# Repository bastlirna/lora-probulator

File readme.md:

# LoRa Probulator

*Yat Another LoRaWAN Tester*

<br>

## Motivation

TBD

## Key Features

- Send LoRaWAN message on button press
- Periodic sending
- Configurable message parameters (confirmation, payload, SF, etc.)
- Multiple device (ABP/OTAA, several keys configuration for testing several network providers)  

For more detail about features see [Firmware project](https://github.com/bastlirna/lora-probulator/projects/1) where are list of all ideas, selected requirements and progress of its implementation.

## Build

### Hardware

What do you need:

- [BOM](hw/bom.md)
- [PCB](https://github.com/bastlirna/lora-probulator/blob/master/hw/pcb/lora-tester-top.png)
- [3D printed enclosure ](https://github.com/bastlirna/lora-probulator/blob/master/hw/enclosure/stl/_full_preview.stl) 

For more detail see [schematics](https://github.com/bastlirna/lora-probulator/blob/master/hw/lora-tester.pdf).

### Firmware

FW is written in [Arduino libraries for ESP32](https://github.com/espressif/arduino-esp32) and build with [PlatformIO](http://platformio.org/).

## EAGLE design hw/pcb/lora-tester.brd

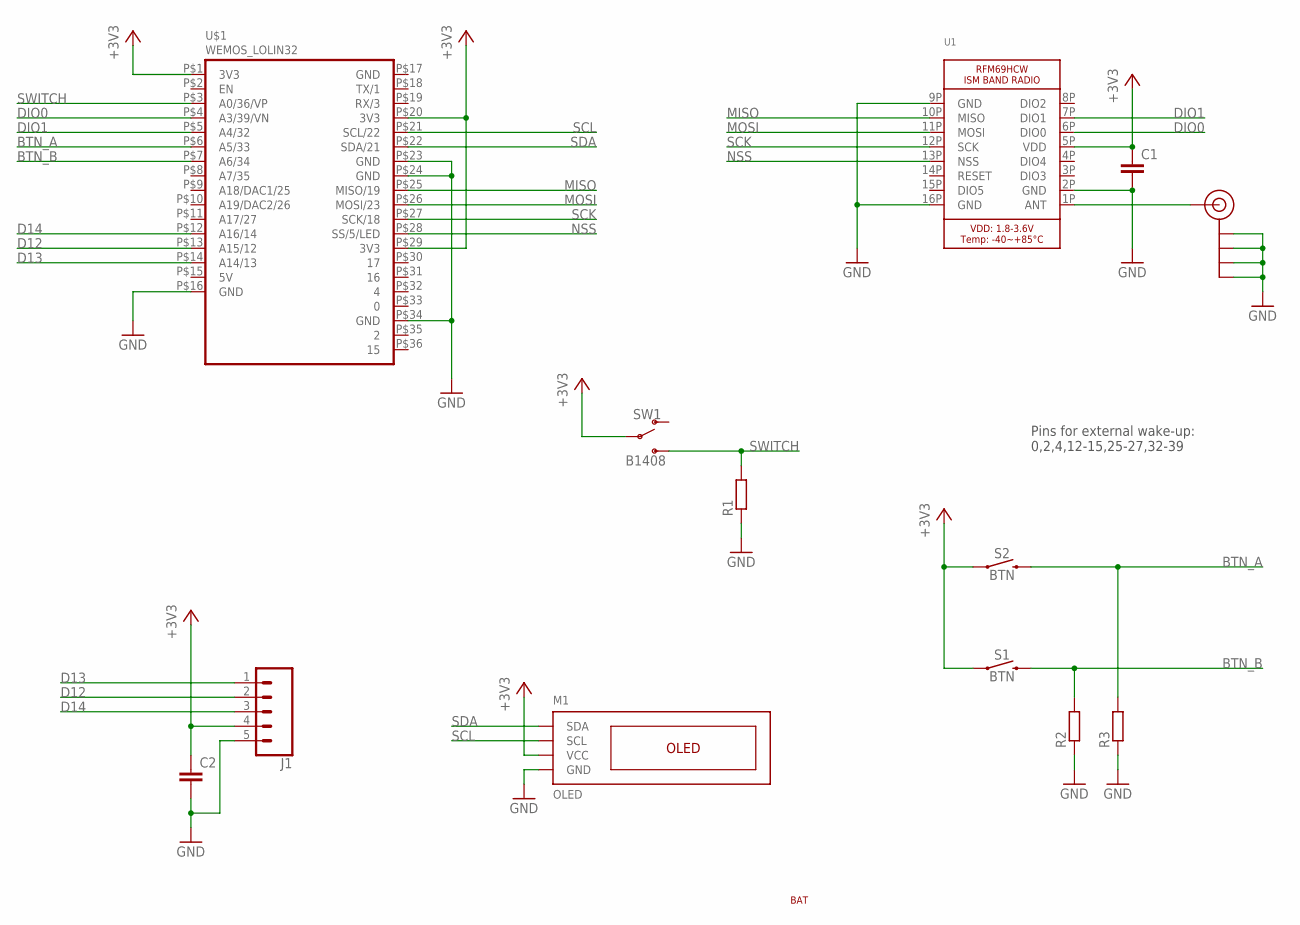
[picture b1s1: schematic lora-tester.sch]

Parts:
BAT: BAT
C1, C2: C-EUC1206; C1206
J1: CONN_05PTH_LONGPADS; 1X05_LONGPADS
J$2: SMA_EDGE; SMA-EDGE
M1: OLED
R1, R2, R3: R-EU_R0805; R0805
S1, S2: BTN; TACTILE_SWITCH_SMD_6.2MM_TALL
SW1: B1408; P-B1408
U1: RFM69HCW_SMT; RFMHCW_SMT
U$1: WEMOS_LOLIN32

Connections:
+3V3: C1.1, C2.1, J1.4, M1.VCC, S1.A2 (1), S2.A2 (1), SW1.P, U1.5P (VDD), U$1.P$1 (3V3), U$1.P$20 (3V3), U$1.P$29 (3V3)
BTN_A: R3.2, S2.B2 (2), U$1.P$6 (A5/33)
BTN_B: R2.2, S1.B2 (2), U$1.P$7 (A6/34)
D12: J1.2, U$1.P$13 (A15/12)
D13: J1.1, U$1.P$14 (A14/13)
D14: J1.3, U$1.P$12 (A16/14)
DIO0: U1.6P (DIO0), U$1.P$4 (A3/39/VN)
DIO1: U1.7P (DIO1), U$1.P$5 (A4/32)
GND: C1.2, C2.2, J1.5, J$2.GND@0 (GND), J$2.GND@1 (GND), J$2.GND@2 (GND), J$2.GND@3 (GND), M1.GND, R1.1, R2.1, R3.1, U1.2P (GND), U1.9P (GND), U1.16P (GND), U$1.P$16 (GND), U$1.P$23 (GND), U$1.P$24 (GND), U$1.P$34 (GND)
MISO: U1.10P (MISO), U$1.P$25 (MISO/19)
MOSI: U1.11P (MOSI), U$1.P$26 (MOSI/23)
unnamed: J$2.SIG (SIGNAL), U1.1P (ANT)
NSS: U1.13P (NSS), U$1.P$28 (SS/5/LED)
SCK: U1.12P (SCK), U$1.P$27 (SCK/18)
SCL: M1.SCL, U$1.P$21 (SCL/22)
SDA: M1.SDA, U$1.P$22 (SDA/21)
SWITCH: R1.2, SW1.S, U$1.P$3 (A0/36/VP)

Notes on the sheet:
Pins for external wake-up: 0,2,4,12-15,25-27,32-39

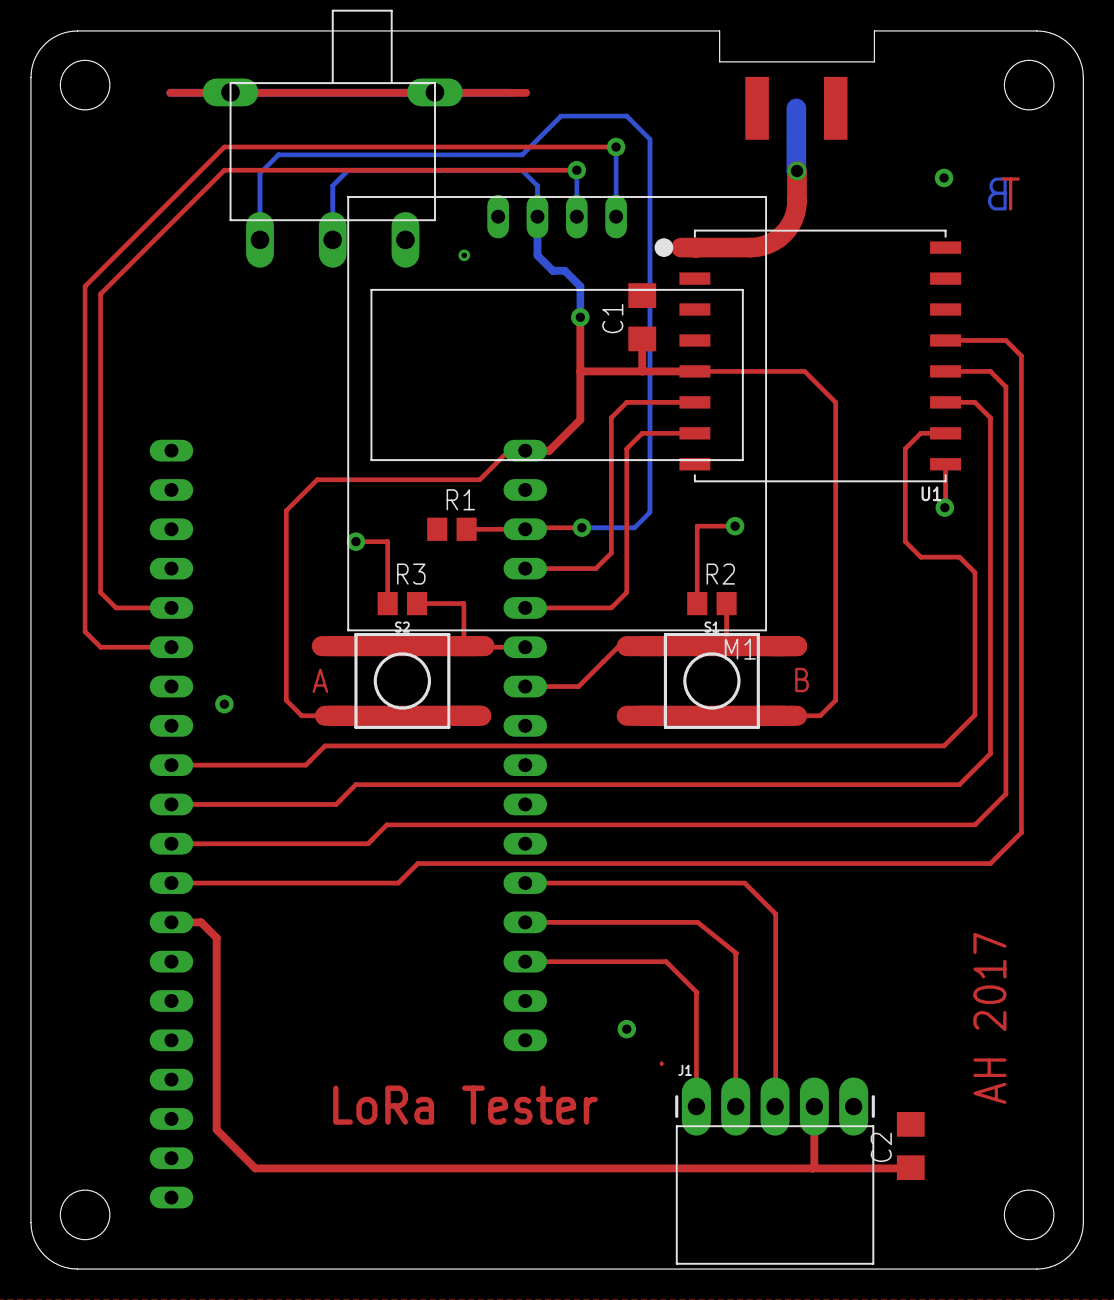
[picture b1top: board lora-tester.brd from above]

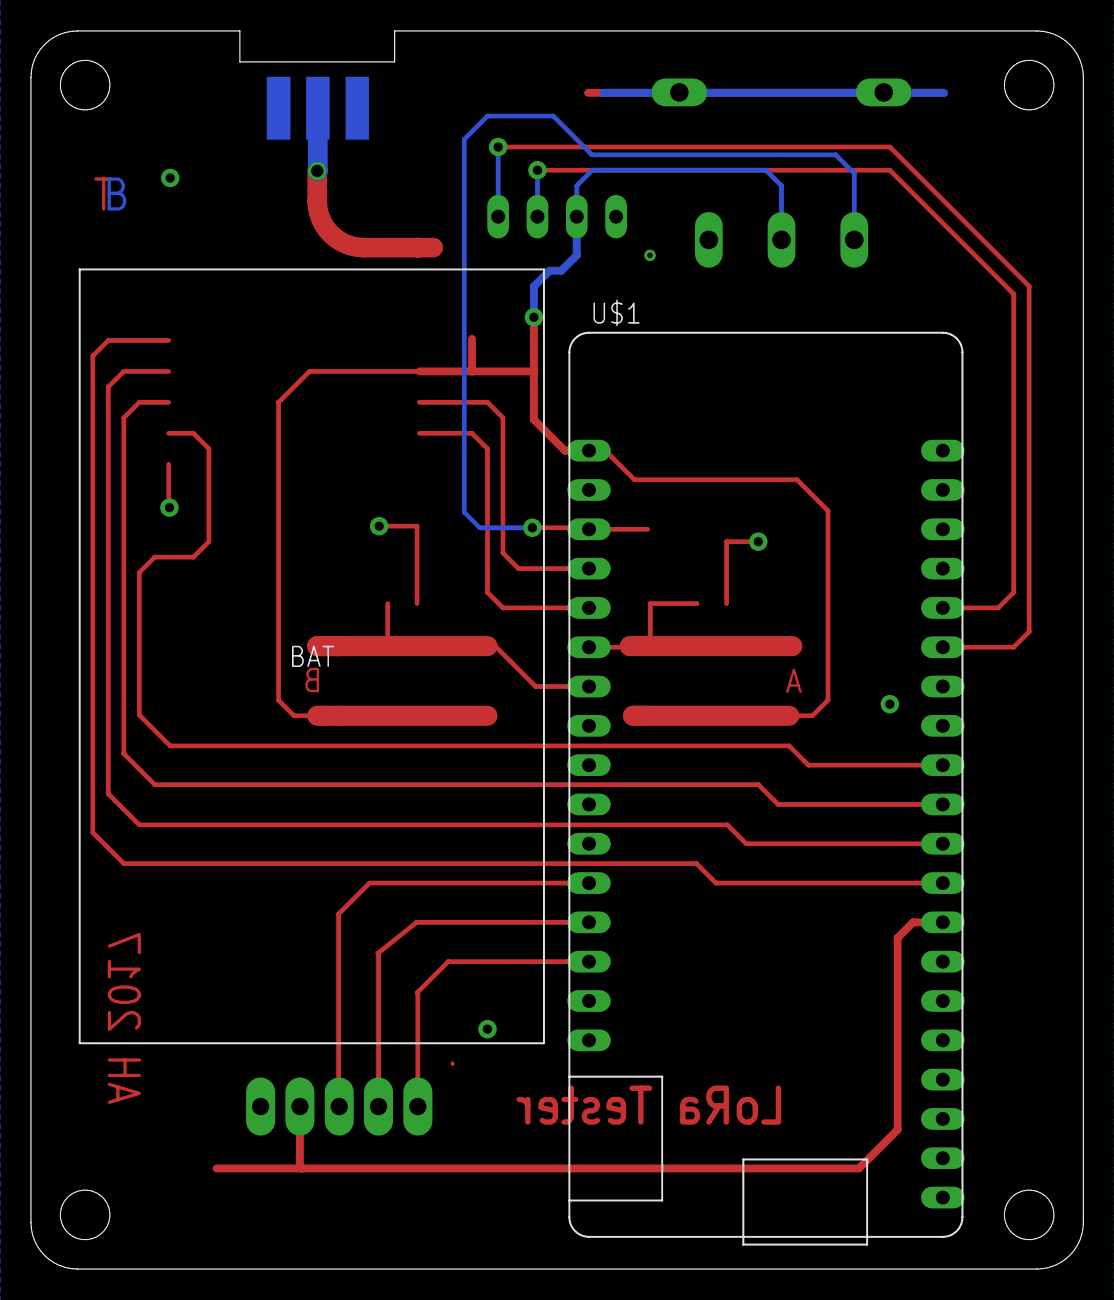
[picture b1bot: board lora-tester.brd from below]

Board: 2 copper layers, 68.0 x 80.0 mm, 14 parts (3 on the bottom side), 17 nets.

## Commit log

2017-11-06 Add almost empty readme file.
2017-11-06 Create LICENSE
2017-11-06 Add schematics and PCB layout
2017-11-06 Add schematics in PDF
2017-11-06 Add enclosure files for 3D printing
2017-11-06 Add dependencies for enclosure (OpenSCAD files)
2017-11-06 STL Preview
2017-11-06 Add PNG image of PCB
2017-11-06 Add photo
2017-11-06 Add photo to readme
2017-11-06 First version of FW
2017-11-06 Move image
2017-11-17 XBM icons
2017-11-17 Improve UI
2017-11-17 More description
2017-11-17 Add bom
2017-11-17 Edit requirements
2017-11-17 Reset stats when device change (fix #3)
2017-11-17 Check switch state before sleep (fix #2)
2017-11-17 Add logging library
2017-11-17 Add screen mirroring (send oled buffer over serial)
2017-11-17 Add tool for mirror screen on PC (show and save images)
2017-11-17 Remove old file
2018-06-10 Add key sample file
2018-06-10 Update gitignore for VSCode
2018-06-10 Add editorconfig for FW
2018-06-10 Add monitor speed into pio file
2018-06-10 Lora fn cleanup
2018-06-10 Fix defualt interval after reset
2018-06-10 Update gitignore for FW
2018-06-10 Add basic payload types
2018-07-03 Improve TX screen
2019-05-20 Add images
2019-10-15 FIX: case-sensitive includes
2019-10-15 FIX: not everyone use windows for build
2019-10-15 FIX: Missing Display size definitions
2019-10-15 FIX: frame data type is uint8_t not char
2019-10-15 FIX: SF settings

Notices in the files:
parts and their libraries:
SparkFun-Switches: Licensing: Creative Commons ShareAlike 4.0 International - https://creativecommons.org/licenses/by-sa/4.0
